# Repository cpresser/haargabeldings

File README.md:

# HaarGabelDings

# Hardware
The current revision uses a SAMD21 MCU, making it compatible with the `Arduino Zero` and the `Adafruit Feather M0 Express`.

Since there was no space left to route tracks or put parts, no other Pins are broken out. Also there is no USB ESD Protection.

## PCB
Export gerbers and order it at you favorite fab.
The first proto used 2mm FR4 instead of the default 1.5mm and is quite usable. Perhaps 3mm is even better.. who knows? One might even try to glue two PCBs together somehow to make the whole thing stiffer.

## Coating?
Some coating is required, otherwise the assembled PCB has to many sharp edges which makes it unusable as a hairpiece. I used epoxy for the prototype. Make sure to mask the switch, debugger-port and USB-connector. You don't want them covered in epoxy (I have been there, don't repeat my mistakes).

## BOM
Nope. I might add one later.

All parts are available at digikey though - assuming there is no global semiconductor supplychain crisis.

## Battery
Connect any single cell lipo battery. I recommend to get one with a build in battery management system.

# Software
The v3 version is supposed to be compatible with the "Adafruit Feather M0 Express", which means one can use micropython.

## USB Bootloader
The Adafruit or Arduino Bootloader should work.

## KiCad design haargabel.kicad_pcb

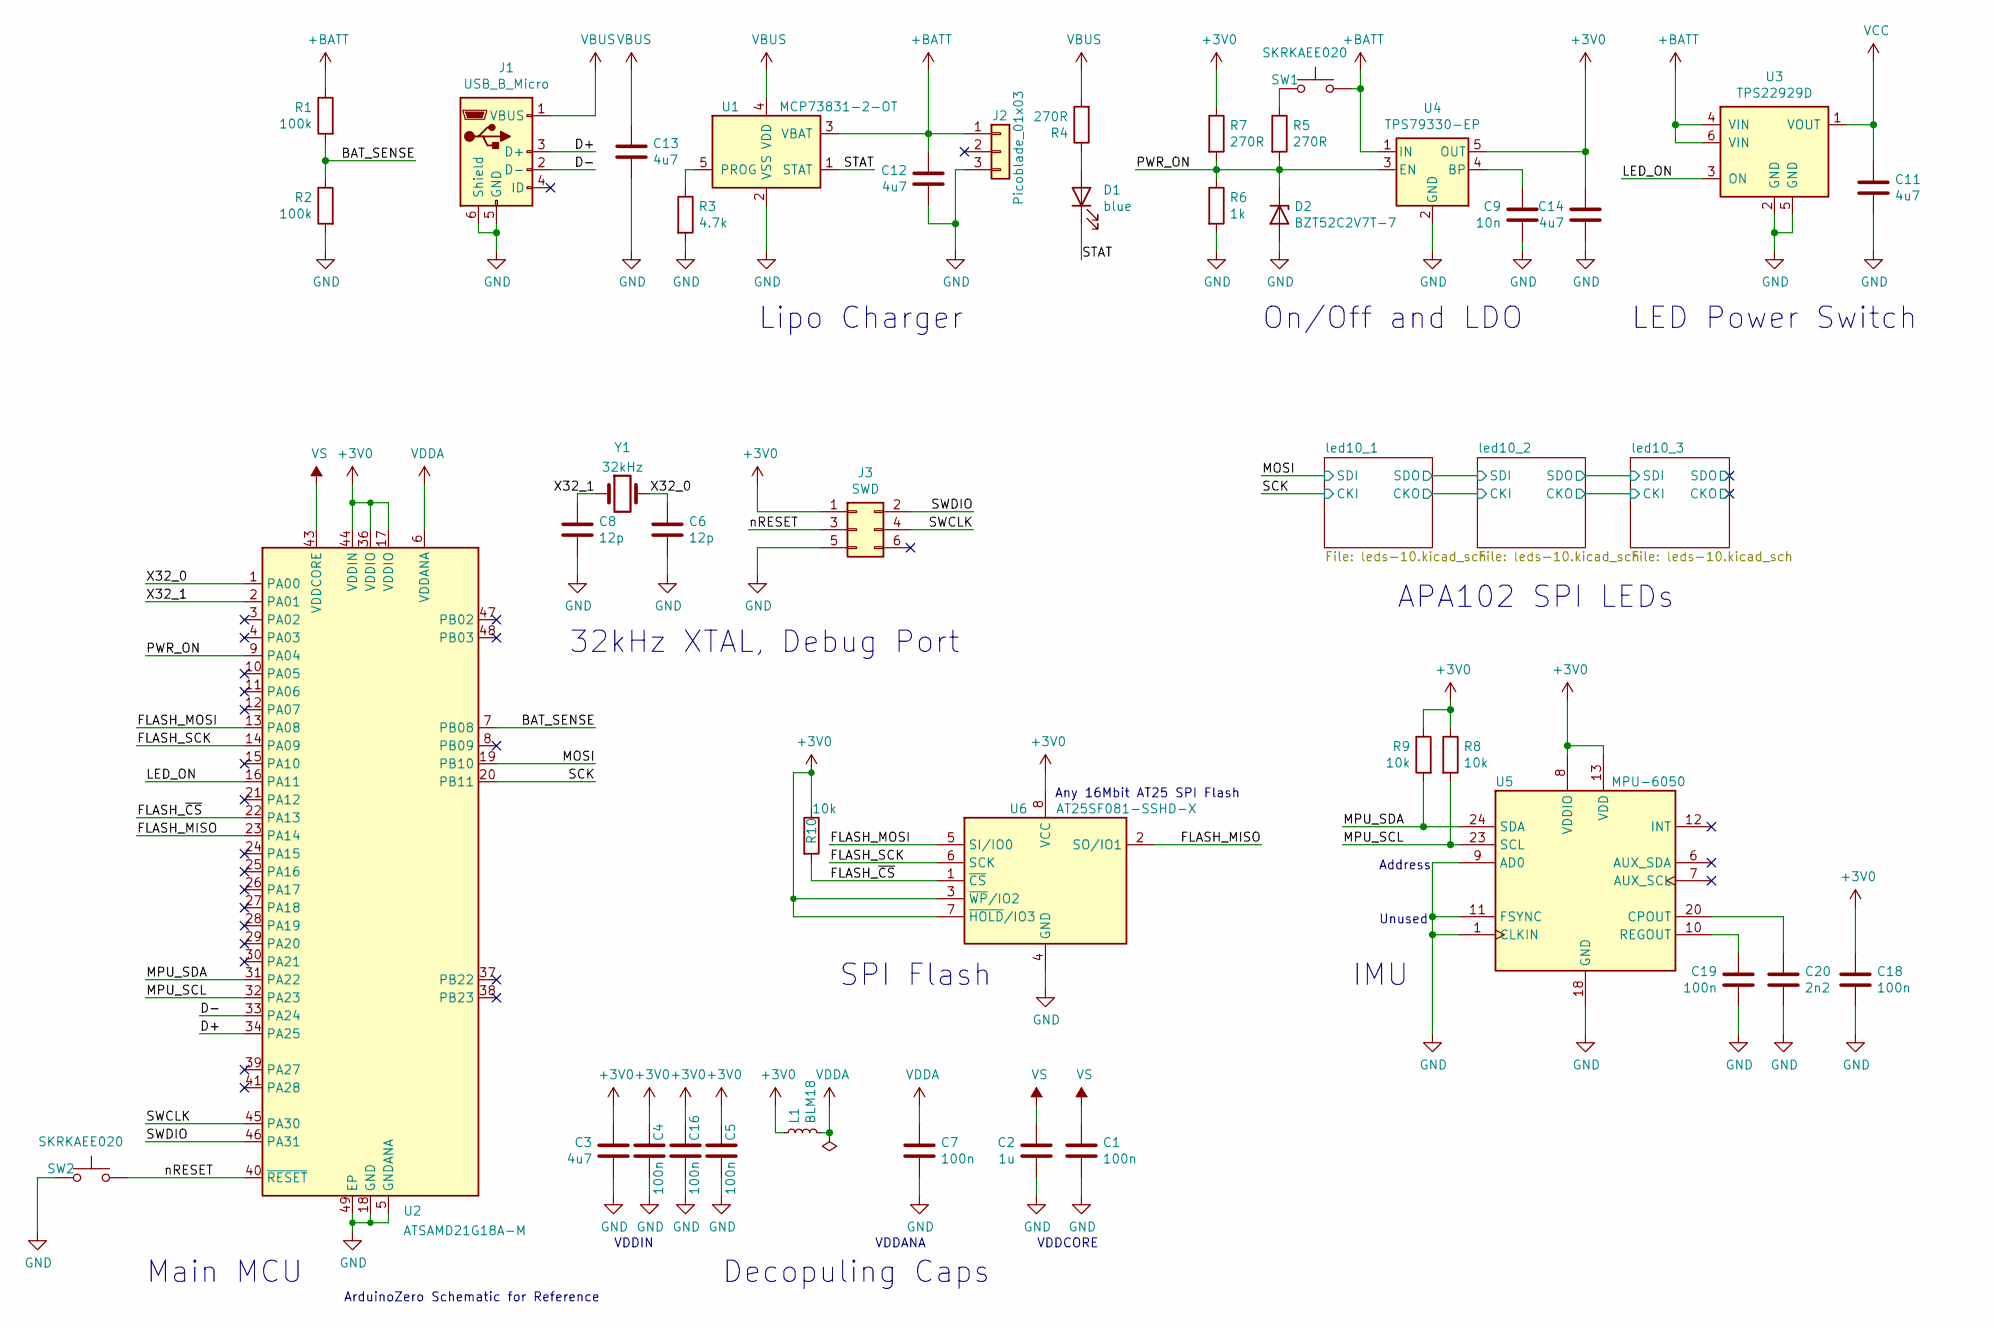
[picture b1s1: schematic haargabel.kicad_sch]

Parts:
C1, C4, C5, C7, C16, C18, C19: 100n; C_0603_1608Metric
C2: 1u; C_0603_1608Metric
C3, C11, C12, C13, C14: 4u7; C_0805_2012Metric
C6, C8: 12p; C_0603_1608Metric
C9: 10n; C_0603_1608Metric
C20: 2n2; C_0603_1608Metric
D1: blue; LED_0603_1608Metric
D2: BZT52C2V7T-7; D_SOD-523
J1: USB_B_Micro; USB_Micro-B_Amphenol_10103594-0001LF_Horizontal
J2: Picoblade_01x03; Molex_PicoBlade_53261-0371_1x03-1MP_P1.25mm_Horizontal
J3: SWD; Tag-Connect_TC2030-IDC-NL_2x03_P1.27mm_Vertical
L1: BLM18; R_0603_1608Metric
R1, R2: 100k; R_0603_1608Metric
R3: 4.7k; R_0603_1608Metric
R4, R5, R7: 270R; R_0603_1608Metric
R6: 1k; R_0603_1608Metric
R8, R9, R10: 10k; R_0603_1608Metric
SW1, SW2: SKRKAEE020; SW_Push_SPST_NO_Alps_SKRK
U1: MCP73831-2-OT; SOT-23-5
U2: ATSAMD21G18A-M; QFN-48-1EP_7x7mm_P0.5mm_EP5.15x5.15mm
U3: TPS22929D; SOT-23-6
U4: TPS79330-EP; SOT-23-5
U5: MPU-6050; InvenSense_QFN-24_4x4mm_P0.5mm
U6: AT25SF081-SSHD-X; SOIC-8_3.9x4.9mm_P1.27mm
Y1: 32kHz; Crystal_SMD_3215-2Pin_3.2x1.5mm

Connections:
+3V0: C3.2, C4.1, C5.1, C14.2, C16.1, C18.1, J3.1, L1.1, R7.1, R8.1, R9.1, R10.1, U2.17 (VDDIO), U2.36 (VDDIO), U2.44 (VDDIN), U4.5 (OUT), U5.8 (VDDIO), U5.13 (VDD), U6.3 (~WP/IO2), U6.7 (~HOLD/IO3), U6.8 (VCC)
+BATT: C12.2, J2.1, R1.1, SW1.1, U1.3 (VBAT), U3.4 (VIN), U3.6 (VIN), U4.1 (IN)
/BAT_SENSE: R1.2, R2.1, U2.7 (PB08)
/D+: J1.3 (D+), U2.34 (PA25)
/D-: J1.2 (D-), U2.33 (PA24)
/FLASH_MISO: U2.23 (PA14), U6.2 (SO/IO1)
/FLASH_MOSI: U2.13 (PA08), U6.5 (SI/IO0)
/FLASH_SCK: U2.14 (PA09), U6.6 (SCK)
/FLASH_~CS: R10.2, U2.22 (PA13), U6.1 (~CS)
/LED_ON: U2.16 (PA11), U3.3 (ON)
/MOSI: U2.19 (PB10); also elsewhere on the board
/MPU_SCL: R8.2, U2.32 (PA23), U5.23 (SCL)
/MPU_SDA: R9.2, U2.31 (PA22), U5.24 (SDA)
/PWR_ON: D2.1 (K), R5.2, R6.1, R7.2, U2.9 (PA04), U4.3 (EN)
/SCK: U2.20 (PB11); also elsewhere on the board
/STAT: D1.1 (K), U1.1 (STAT)
/SWCLK: J3.4, U2.45 (PA30)
/SWDIO: J3.2, U2.46 (PA31)
/X32_0: C6.1, U2.1 (PA00), Y1.2
/X32_1: C8.1, U2.2 (PA01), Y1.1
/nRESET: J3.3, SW2.1, U2.40 (~RESET)
GND: C1.2, C2.2, C3.1, C4.2, C5.2, C6.2, C7.2, C8.2, C9.1, C11.1, C12.1, C13.2, C14.1, C16.2, C18.2, C19.2, C20.2, D2.2 (A), J1.5 (GND), J1.6 (Shield), J2.3, J3.5, R2.2, R3.2, R6.2, SW2.2, U1.2 (VSS), U2.5 (GNDANA), U2.18 (GND), U2.35 (GND), U2.42 (GND), U2.49 (EP), U3.2 (GND), U3.5 (GND), U4.2 (GND), U5.1 (CLKIN), U5.9 (AD0), U5.11 (FSYNC), U5.18 (GND), U6.4 (GND); also elsewhere on the board
unnamed: D1.2 (A), R4.1
unnamed: R5.1, SW1.2
unnamed: R3.1, U1.5 (PROG)
unnamed: C9.2, U4.4 (BP)
unnamed: C20.1, U5.20 (CPOUT)
unnamed: C19.1, U5.10 (REGOUT)
VBUS: C13.1, J1.1 (VBUS), R4.2, U1.4 (VDD)
VCC: C11.2, U3.1 (VOUT); also elsewhere on the board
VDDA: C7.1, L1.2, U2.6 (VDDANA)
VS: C1.1, C2.1, U2.43 (VDDCORE)

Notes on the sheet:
32kHz XTAL, Debug Port
Unused
On/Off and LDO
VDDCORE
SPI Flash
ArduinoZero Schematic for Reference
Lipo Charger
Decopuling Caps
VDDIN
LED Power Switch
Address
Main MCU
APA102 SPI LEDs
VDDANA
IMU
Any 16Mbit AT25 SPI Flash

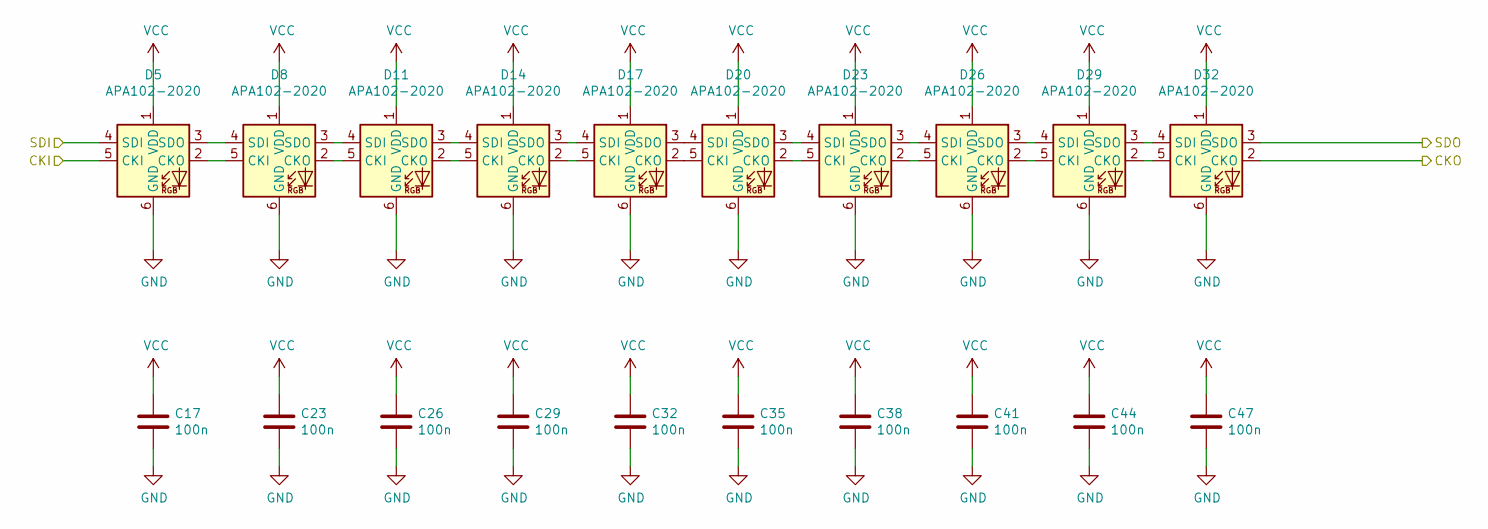
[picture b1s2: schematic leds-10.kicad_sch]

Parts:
C17, C23, C26, C29, C32, C35, C38, C41, C44, C47: 100n; C_0603_1608Metric
D5, D8, D11, D14, D17, D20, D23, D26, D29, D32: APA102-2020; LED-APA102-2020

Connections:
/MOSI: D5.4 (SDI); also elsewhere on the board
/SCK: D5.5 (CKI); also elsewhere on the board
/led10_1/CKO: D32.2 (CKO); also elsewhere on the board
/led10_1/SDO: D32.3 (SDO); also elsewhere on the board
GND: C17.2, C23.2, C26.2, C29.2, C32.2, C35.2, C38.2, C41.2, C44.2, C47.2, D5.6 (GND), D8.6 (GND), D11.6 (GND), D14.6 (GND), D17.6 (GND), D20.6 (GND), D23.6 (GND), D26.6 (GND), D29.6 (GND), D32.6 (GND); also elsewhere on the board
unnamed: D5.2 (CKO), D8.5 (CKI)
unnamed: D5.3 (SDO), D8.4 (SDI)
unnamed: D8.2 (CKO), D11.5 (CKI)
unnamed: D11.2 (CKO), D14.5 (CKI)
unnamed: D8.3 (SDO), D11.4 (SDI)
unnamed: D11.3 (SDO), D14.4 (SDI)
unnamed: D14.2 (CKO), D17.5 (CKI)
unnamed: D14.3 (SDO), D17.4 (SDI)
unnamed: D17.2 (CKO), D20.5 (CKI)
unnamed: D17.3 (SDO), D20.4 (SDI)
unnamed: D20.2 (CKO), D23.5 (CKI)
unnamed: D20.3 (SDO), D23.4 (SDI)
unnamed: D23.2 (CKO), D26.5 (CKI)
unnamed: D23.3 (SDO), D26.4 (SDI)
unnamed: D26.2 (CKO), D29.5 (CKI)
unnamed: D26.3 (SDO), D29.4 (SDI)
unnamed: D29.2 (CKO), D32.5 (CKI)
unnamed: D29.3 (SDO), D32.4 (SDI)
VCC: C17.1, C23.1, C26.1, C29.1, C32.1, C35.1, C38.1, C41.1, C44.1, C47.1, D5.1 (VDD), D8.1 (VDD), D11.1 (VDD), D14.1 (VDD), D17.1 (VDD), D20.1 (VDD), D23.1 (VDD), D26.1 (VDD), D29.1 (VDD), D32.1 (VDD); also elsewhere on the board

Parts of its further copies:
C10, C15, C21, C22, C24, C25, C27, C28, C30, C31, C33, C34, C36, C37, C39, C40, C42, C43, C45, C46: 100n; C_0603_1608Metric
D3, D4, D6, D7, D9, D10, D12, D13, D15, D16, D18, D19, D21, D22, D24, D25, D27, D28, D30, D31: APA102-2020; LED-APA102-2020

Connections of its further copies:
/led10_1/CKO: D4.5 (CKI); also elsewhere on the board
/led10_1/SDO: D4.4 (SDI); also elsewhere on the board
/led10_2/CKO: D3.5 (CKI), D31.2 (CKO)
/led10_2/SDO: D3.4 (SDI), D31.3 (SDO)
/led10_3/CKO: D30.2 (CKO)
/led10_3/SDO: D30.3 (SDO)
GND: C10.2, C15.2, C21.2, C22.2, C24.2, C25.2, C27.2, C28.2, C30.2, C31.2, C33.2, C34.2, C36.2, C37.2, C39.2, C40.2, C42.2, C43.2, C45.2, C46.2, D3.6 (GND), D4.6 (GND), D6.6 (GND), D7.6 (GND), D9.6 (GND), D10.6 (GND), D12.6 (GND), D13.6 (GND), D15.6 (GND), D16.6 (GND), D18.6 (GND), D19.6 (GND), D21.6 (GND), D22.6 (GND), D24.6 (GND), D25.6 (GND), D27.6 (GND), D28.6 (GND), D30.6 (GND), D31.6 (GND); also elsewhere on the board
unnamed: D3.2 (CKO), D6.5 (CKI)
unnamed: D3.3 (SDO), D6.4 (SDI)
unnamed: D4.2 (CKO), D7.5 (CKI)
unnamed: D4.3 (SDO), D7.4 (SDI)
unnamed: D6.2 (CKO), D9.5 (CKI)
unnamed: D6.3 (SDO), D9.4 (SDI)
unnamed: D7.2 (CKO), D10.5 (CKI)
unnamed: D10.2 (CKO), D13.5 (CKI)
unnamed: D7.3 (SDO), D10.4 (SDI)
unnamed: D10.3 (SDO), D13.4 (SDI)
unnamed: D9.2 (CKO), D12.5 (CKI)
unnamed: D12.2 (CKO), D15.5 (CKI)
unnamed: D9.3 (SDO), D12.4 (SDI)
unnamed: D12.3 (SDO), D15.4 (SDI)
unnamed: D13.2 (CKO), D16.5 (CKI)
unnamed: D13.3 (SDO), D16.4 (SDI)
unnamed: D15.2 (CKO), D18.5 (CKI)
unnamed: D15.3 (SDO), D18.4 (SDI)
unnamed: D16.2 (CKO), D19.5 (CKI)
unnamed: D16.3 (SDO), D19.4 (SDI)
unnamed: D18.2 (CKO), D21.5 (CKI)
unnamed: D18.3 (SDO), D21.4 (SDI)
unnamed: D19.2 (CKO), D22.5 (CKI)
unnamed: D19.3 (SDO), D22.4 (SDI)
unnamed: D21.2 (CKO), D24.5 (CKI)
unnamed: D21.3 (SDO), D24.4 (SDI)
unnamed: D22.2 (CKO), D25.5 (CKI)
unnamed: D22.3 (SDO), D25.4 (SDI)
unnamed: D24.2 (CKO), D27.5 (CKI)
unnamed: D24.3 (SDO), D27.4 (SDI)
unnamed: D25.2 (CKO), D28.5 (CKI)
unnamed: D25.3 (SDO), D28.4 (SDI)
unnamed: D27.2 (CKO), D30.5 (CKI)
unnamed: D27.3 (SDO), D30.4 (SDI)
unnamed: D28.2 (CKO), D31.5 (CKI)
unnamed: D28.3 (SDO), D31.4 (SDI)
VCC: C10.1, C15.1, C21.1, C22.1, C24.1, C25.1, C27.1, C28.1, C30.1, C31.1, C33.1, C34.1, C36.1, C37.1, C39.1, C40.1, C42.1, C43.1, C45.1, C46.1, D3.1 (VDD), D4.1 (VDD), D6.1 (VDD), D7.1 (VDD), D9.1 (VDD), D10.1 (VDD), D12.1 (VDD), D13.1 (VDD), D15.1 (VDD), D16.1 (VDD), D18.1 (VDD), D19.1 (VDD), D21.1 (VDD), D22.1 (VDD), D24.1 (VDD), D25.1 (VDD), D27.1 (VDD), D28.1 (VDD), D30.1 (VDD), D31.1 (VDD); also elsewhere on the board

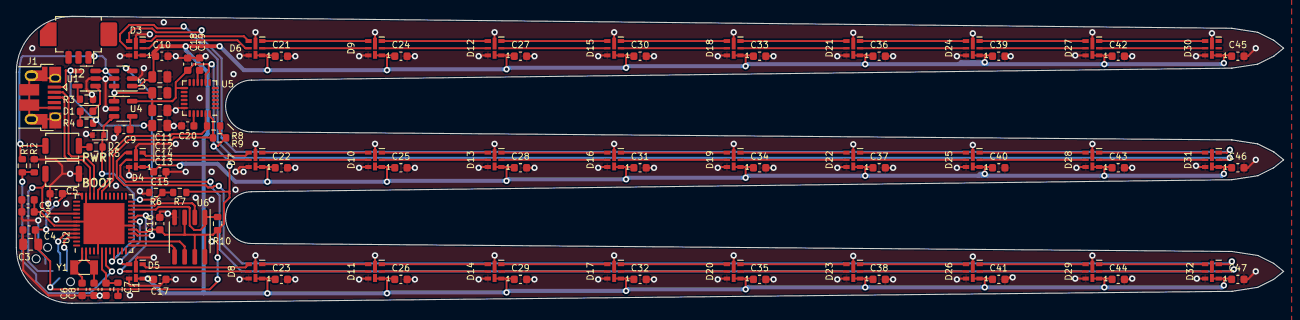
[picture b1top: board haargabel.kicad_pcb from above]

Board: 2 copper layers, 159.0 x 36.0 mm, 102 parts (1 on the bottom side), 90 nets.

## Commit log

2019-04-10 Better B.SilkS text
2019-04-10 Remove Backup-File
2019-05-30 Fix startup circuit
    Use a zener-diode instead of just resistors.
    This makes stuff much easier since it 'protects' the CPU from the high battery voltage.
2019-05-30 Remove the DIY-Panel, make it more pointy
    The Fab will fuck up the routing anyway. Lets just hope they place the tabs somewhat reasonable.
    The round ends were not pointy enough, fix them.
2019-05-30 Make it longer
    Add two more LEDs, making the whole thing 30mm longer
2019-05-30 Re-Annotate, so the LED numbering makes more sense
2019-05-30 Add minimal documentation
2019-05-31 Move bottom silkscreen
2020-10-17 Add schematic as doc/haargabel.pdf
2022-03-27 Use a different MCU to make programming easier
2022-03-27 Add Silkscreen for the buttons
2022-03-27 Fix render.png image
2022-03-27 Fix render.png image again
2022-03-27 Remove .net file, v6 does not need it
2022-03-27 Remove .pro file, v6 does not need it
2022-03-30 Fix wording in README
2023-05-23 Convert to KiCad7, add iBOM
2023-05-23 Simplify component values
